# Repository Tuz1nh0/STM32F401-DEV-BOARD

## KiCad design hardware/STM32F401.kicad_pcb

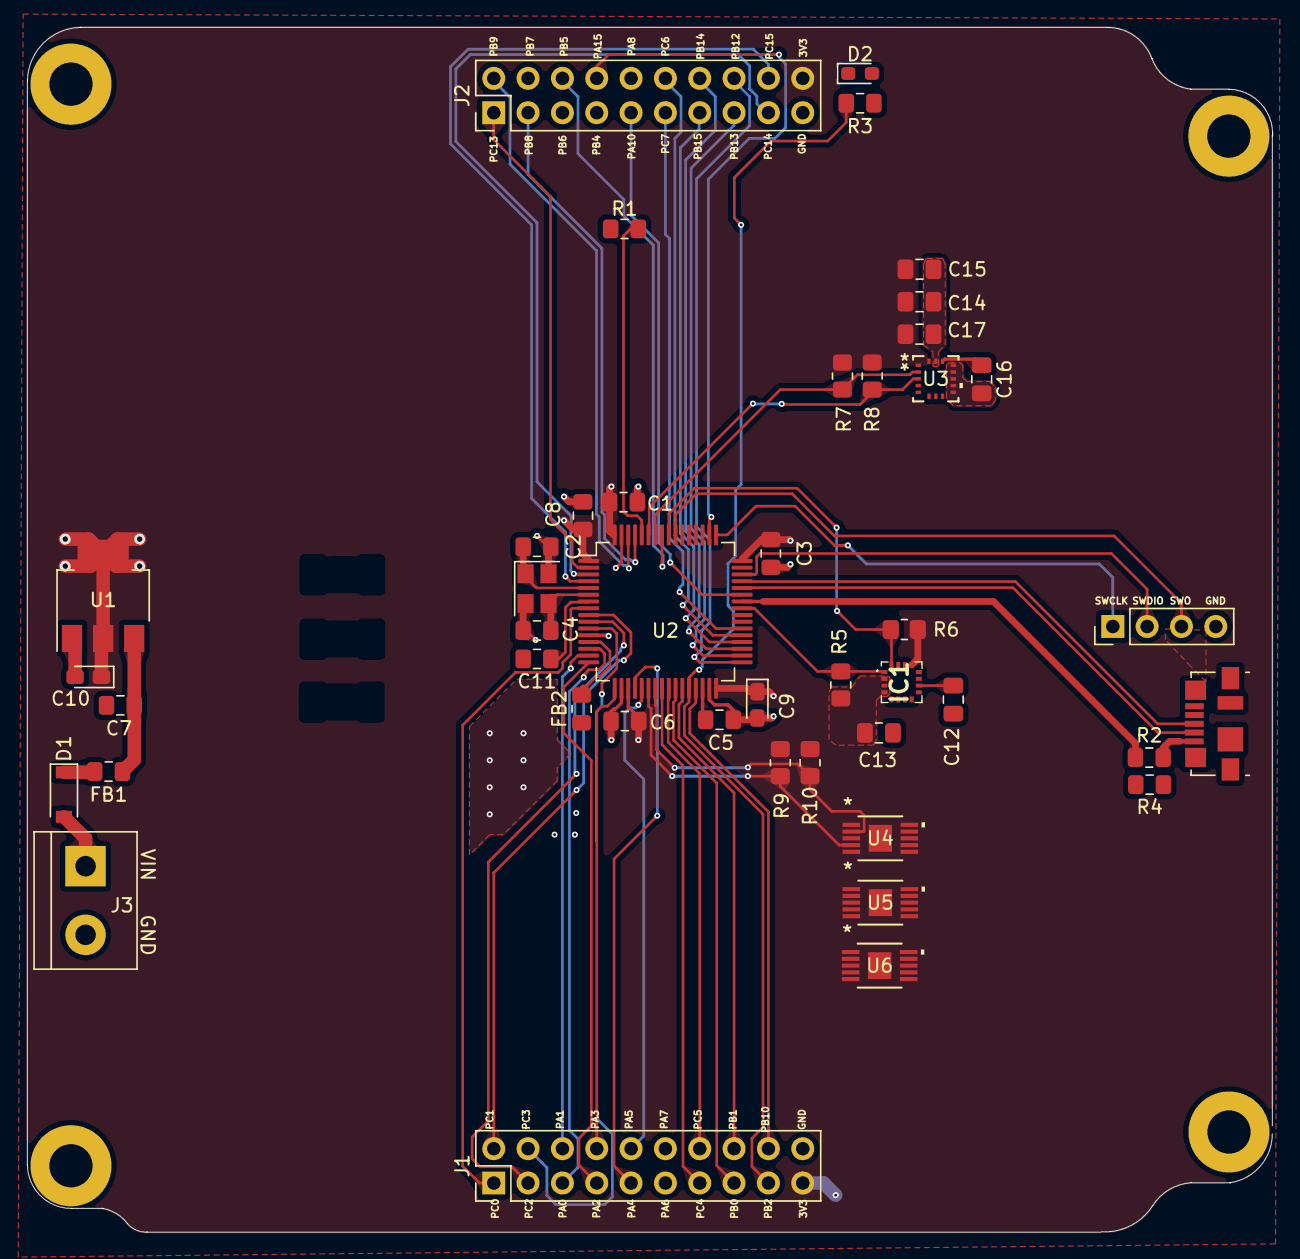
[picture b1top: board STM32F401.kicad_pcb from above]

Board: 4 copper layers, 92.1 x 89.1 mm, 44 parts (0 on the bottom side), 63 nets.

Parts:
C1, C3, C6, C8: 100nF; C_0805_2012Metric_Pad1.15x1.40mm_HandSolder
C2, C4: 12pF; C_0805_2012Metric_Pad1.15x1.40mm_HandSolder
C5: 2.2uF; C_0805_2012Metric_Pad1.15x1.40mm_HandSolder
C7, C11: 10uF; C_0805_2012Metric_Pad1.15x1.40mm_HandSolder
C9: 4.7uF; CP_EIA-2012-12_Kemet-R_Pad1.30x1.05mm_HandSolder
C10: 22uF; CP_EIA-2012-12_Kemet-R_Pad1.30x1.05mm_HandSolder
C12, C13, C14, C15, C16, C17: C_0805_2012Metric_Pad1.18x1.45mm_HandSolder
D1: B5819W; D_SOD-123
D2: LED_Small; LED_0603_1608Metric_Pad1.05x0.95mm_HandSolder
FB1, FB2: 100 ohms; L_0805_2012Metric_Pad1.15x1.40mm_HandSolder
HSE1: 16Mhz; Crystal_SMD_3225-4Pin_3.2x2.5mm
IC1: MMC5983MA
J1, J2: Conn_02x10_Odd_Even; PinHeader_2x10_P2.54mm_Vertical
J3: POWER; TerminalBlock_bornier-2_P5.08mm
J4: USB_B_Micro; USB_Micro-B_Molex_47346-0001
J5: Conn_01x04; PinHeader_1x04_P2.54mm_Vertical
R1: 10k; R_0805_2012Metric_Pad1.15x1.40mm_HandSolder
R2, R3: 220; R_0805_2012Metric_Pad1.15x1.40mm_HandSolder
R4: 330; R_0805_2012Metric_Pad1.15x1.40mm_HandSolder
R5, R6, R7, R8, R9, R10: R_0805_2012Metric_Pad1.20x1.40mm_HandSolder
U1: AMS1117-3.3; SOT-223-3_TabPin2
U2: STM32F401RCTx; LQFP-64_10x10mm_P0.5mm
U3: IAM-20380; IAM-20380_IVS
U4, U5, U6: A3909GLYTR-T; A3909GLYTR-T_ALM

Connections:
+3V3: C1.1, C3.1, C6.1, C8.1, C9.1, C10.1, C13.1, C14.1, C15.1, C17.1, IC1.2 (VDD), IC1.4 (SPI_CS), IC1.13 (VDDIO), J1.19, J2.20, R5.1, R6.1, R7.1, R8.1, R9.1, R10.1, U1.2 (VO), U2.1 (VBAT), U2.19 (VDD), U2.32 (VDD), U2.48 (VDD), U2.64 (VDD), U3.1 (VDDIO), U3.16 (VDD)
+12V: U4.3, U5.3, U6.3
/+MAGTORQ1: U4.7, U4.10
/+MAGTORQ2: U5.7, U5.10
/+MAGTORQ3: U6.7, U6.10
/-MAGTORQ1: U4.6, U4.9
/-MAGTORQ2: U5.6, U5.9
/-MAGTORQ3: U6.6, U6.9
BOOT0: R1.1, U2.60 (BOOT0)
GND: C1.2, C2.2, C3.2, C4.2, C5.2, C6.2, C7.2, C8.2, C9.2, C10.2, C11.2, C12.2, C13.2, C14.2, C15.2, C16.2, C17.2, D2.1 (K), HSE1.2 (G), HSE1.4 (G), IC1.9 (GND_1), IC1.11 (GND_2), J1.20, J2.19, J3.2, J4.5 (GND), J5.4, R1.2, R4.1, U1.1 (GND), U2.12 (VSSA), U2.18 (VSS), U2.31 (VSS), U2.47 (VSS), U2.63 (VSS), U3.9 (RESV), U3.10 (RESV), U3.11 (RESV), U3.12 (RESV), U3.13 (GND), U3.15 (RESV), U4.8, U4.EPAD, U5.8, U5.EPAD, U6.8, U6.EPAD
HSE_IN: C2.1, HSE1.1, U2.5 (PH0)
HSE_OUT: C4.1, HSE1.3, U2.6 (PH1)
I2C1_SCL: R7.2, U2.58 (PB6), U3.2 (SCL/SPC)
I2C1_SDA: R8.2, U2.59 (PB7), U3.3 (SDA/SDI)
I2C3_SCL: IC1.1 (SCL/SPI_SCK), R5.2, U2.41 (PA8)
I2C3_SDA: IC1.16 (SDA/SPI_SDI), R6.2, U2.56 (PB4)
NRST: C11.1, U2.7 (NRST)
unnamed: D1.1 (K), FB1.2
unnamed: D2.2 (A), R3.2
unnamed: C12.1, IC1.10 (CAP)
unnamed: J4.1 (VBUS), R2.2
unnamed: C7.1, FB1.1, U1.3 (VI)
unnamed: FB2.2, U2.13 (VREF+)
unnamed: C16.1, U3.14 (REGOUT)
PA0: J1.5, U2.14 (PA0)
PA1: J1.6, U2.15 (PA1)
PA2: J1.7, U2.16 (PA2)
PA3: J1.8, U2.17 (PA3)
PA4: J1.9, U2.20 (PA4)
PA5: J1.10, U2.21 (PA5)
PA6: R9.2, U2.22 (PA6), U4.1, U4.4, U5.1, U5.4, U6.1, U6.4
PA7: R10.2, U2.23 (PA7), U4.2, U4.5, U5.2, U5.5, U6.2, U6.5
PA10: J2.9, U2.43 (PA10)
PA15: J2.8, U2.50 (PA15)
PB0: J1.15, U2.26 (PB0)
PB1: J1.16, U2.27 (PB1)
PB2: J1.17, R3.1, U2.28 (PB2)
PB5: J2.6, U2.57 (PB5)
PB8: J2.3, U2.61 (PB8)
PB9: J2.2, U2.62 (PB9)
PB10: J1.18, U2.29 (PB10)
PB12: J2.16, U2.33 (PB12)
PB13: J2.15, U2.34 (PB13)
PB14: J2.14, U2.35 (PB14)
PB15: J2.13, U2.36 (PB15)
PC0: J1.1, U2.8 (PC0)
PC1: J1.2, U2.9 (PC1)
PC2: J1.3, U2.10 (PC2)
PC3: J1.4, U2.11 (PC3)
PC4: J1.13, U2.24 (PC4)
PC5: J1.14, U2.25 (PC5)
PC6: J2.12, U2.37 (PC6)
PC7: J2.11, U2.38 (PC7)
PC13: J2.1, U2.2 (PC13)
PC14: J2.17, U2.3 (PC14)
PC15: J2.18, U2.4 (PC15)
SWCLK: J5.1, U2.49 (PA14)
SWDIO: J5.2, U2.46 (PA13)
SWO: J5.3, U2.55 (PB3)
USB_N: J4.2 (D-), U2.44 (PA11)
USB_P: J4.3 (D+), U2.45 (PA12)
USB_VBUS: R2.1, R4.2, U2.42 (PA9)
VDD_IN: D1.2 (A), J3.1
